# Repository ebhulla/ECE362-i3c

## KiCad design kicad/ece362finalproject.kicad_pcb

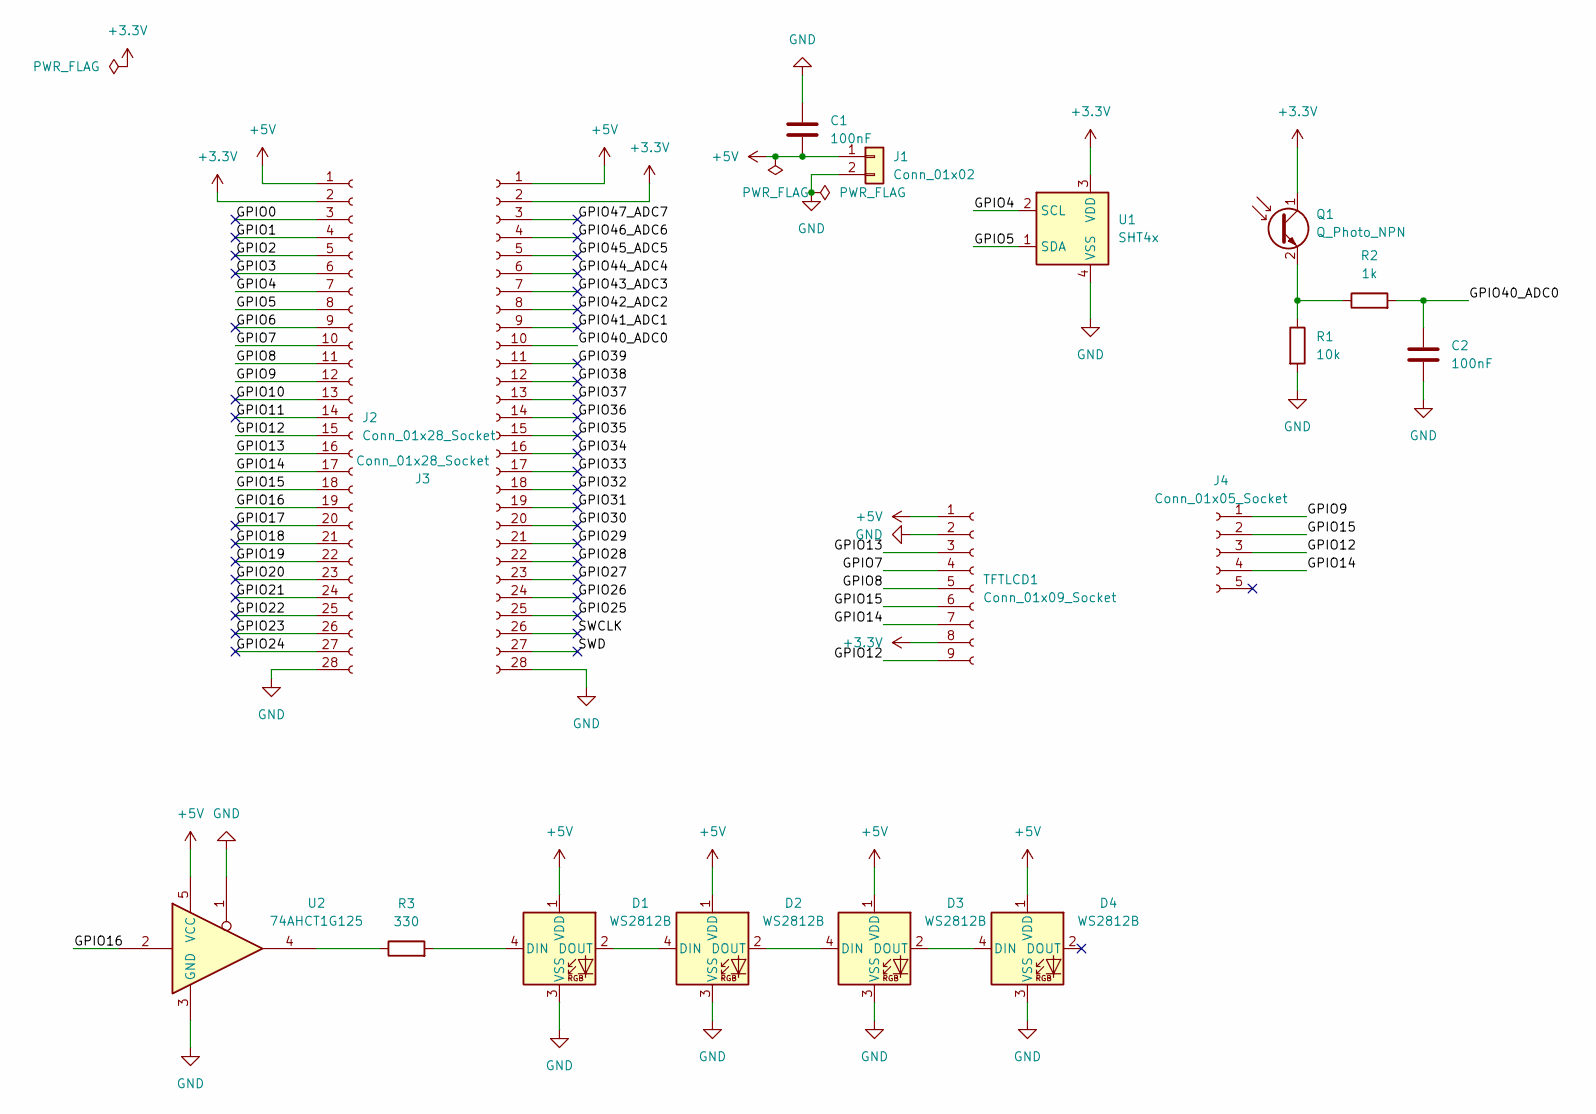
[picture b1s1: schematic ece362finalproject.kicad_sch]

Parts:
C1, C2: 100nF; C_0402_1005Metric
D1, D2, D3, D4: WS2812B; LED_WS2812B_PLCC4_5.0x5.0mm_P3.2mm
J1: Conn_01x02; JST_EH_B2B-EH-A_1x02_P2.50mm_Vertical
J2, J3: Conn_01x28_Socket; PinSocket_1x28_P2.54mm_Vertical
J4: Conn_01x05_Socket; PinSocket_1x05_P2.54mm_Vertical
Q1: Q_Photo_NPN; PT204
R1: 10k; R_0805_2012Metric
R2: 1k; R_0805_2012Metric
R3: 330; R_0805_2012Metric
TFTLCD1: Conn_01x09_Socket; PinSocket_1x09_P2.54mm_Vertical
U1: SHT4x; Sensirion_DFN-4_1.5x1.5mm_P0.8mm_SHT4x_NoCentralPad
U2: 74AHCT1G125; SOT25_DIO

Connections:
+3.3V: J2.2, J3.2, Q1.1 (C), TFTLCD1.8, U1.3 (VDD)
+5V: C1.2, D1.1 (VDD), D2.1 (VDD), D3.1 (VDD), D4.1 (VDD), J1.1, J2.1, J3.1, TFTLCD1.1, U2.5 (VCC)
/GPIO0: J2.3
/GPIO1: J2.4
/GPIO2: J2.5
/GPIO3: J2.6
/GPIO4: J2.7, U1.2 (SCL)
/GPIO5: J2.8, U1.1 (SDA)
/GPIO6: J2.9
/GPIO7: J2.10, TFTLCD1.4
/GPIO8: J2.11, TFTLCD1.5
/GPIO9: J2.12, J4.1
/GPIO10: J2.13
/GPIO11: J2.14
/GPIO12: J2.15, J4.3, TFTLCD1.9
/GPIO13: J2.16, TFTLCD1.3
/GPIO14: J2.17, J4.4, TFTLCD1.7
/GPIO15: J2.18, J4.2, TFTLCD1.6
/GPIO16: J2.19, U2.2
/GPIO17: J2.20
/GPIO18: J2.21
/GPIO19: J2.22
/GPIO20: J2.23
/GPIO21: J2.24
/GPIO22: J2.25
/GPIO23: J2.26
/GPIO24: J2.27
/GPIO25: J3.25
/GPIO26: J3.24
/GPIO27: J3.23
/GPIO28: J3.22
/GPIO29: J3.21
/GPIO30: J3.20
/GPIO31: J3.19
/GPIO32: J3.18
/GPIO33: J3.17
/GPIO34: J3.16
/GPIO35: J3.15
/GPIO36: J3.14
/GPIO37: J3.13
/GPIO38: J3.12
/GPIO39: J3.11
/GPIO40_ADC0: C2.1, J3.10, R2.2
/GPIO41_ADC1: J3.9
/GPIO42_ADC2: J3.8
/GPIO43_ADC3: J3.7
/GPIO44_ADC4: J3.6
/GPIO45_ADC5: J3.5
/GPIO46_ADC6: J3.4
/GPIO47_ADC7: J3.3
/SWCLK: J3.26
/SWD: J3.27
GND: C1.1, C2.2, D1.3 (VSS), D2.3 (VSS), D3.3 (VSS), D4.3 (VSS), J1.2, J2.28, J3.28, R1.2, TFTLCD1.2, U1.4 (VSS), U2.1, U2.3 (GND)
unnamed: D1.4 (DIN), R3.2
unnamed: D1.2 (DOUT), D2.4 (DIN)
unnamed: D2.2 (DOUT), D3.4 (DIN)
unnamed: D3.2 (DOUT), D4.4 (DIN)
unnamed: Q1.2 (E), R1.1, R2.1
unnamed: R3.1, U2.4

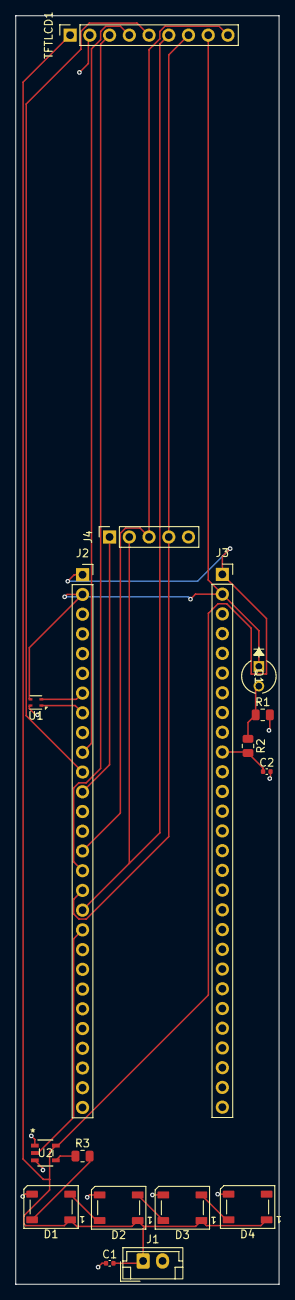
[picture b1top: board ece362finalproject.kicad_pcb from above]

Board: 2 copper layers, 33.9 x 163.3 mm, 17 parts (0 on the bottom side), 20 nets.
